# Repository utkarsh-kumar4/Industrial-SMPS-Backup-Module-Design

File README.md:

<h1>⚡ Industrial SMPS Backup Module Design ⚡</h1>

<h2>Project Premise</h2>
<p>
This project implements a reliable SMPS-based backup system designed to provide clean and stable DC power to industrial electronics such as PLCs, HMIs, sensors, and low-voltage control circuits. In industrial environments, especially in oil & gas, power generation, and transmission systems, voltage stability and low ripple are critical for the safe and accurate operation of automation and control devices. 
The system combines a <strong>TLV61048 boost converter</strong> with a <strong>TLV767-1A LDO regulator</strong> to deliver both voltage elevation and high-quality regulation, ensuring operational reliability even under fluctuating input conditions.
</p>

<h2>Technical Rationale for Module Selection</h2>
<p>
The <strong>TLV61048</strong> was selected for its ability to efficiently boost a low-voltage battery input (e.g., 3.7–12V Li-ion) to the required system bus voltage, maintaining continuous operation even during battery discharge. Its high efficiency (up to 95%) minimizes energy loss and heat generation, which is critical in compact backup systems.  
The <strong>TLV767-1A LDO regulator</strong> is used to post-regulate the boosted voltage, providing low-noise, stable DC output. This stage is essential because boost converters inherently produce high-frequency ripple, which can disrupt sensitive electronics. By combining these stages, the design achieves both efficient energy conversion and superior voltage quality.
</p>

<h2>System Architecture and Operation</h2>
<p>
The architecture consists of two primary stages:
<ul>
  <li><strong>Boost Stage:</strong> Elevates battery voltage to a constant bus voltage suitable for downstream devices, compensating for battery voltage drops.</li>
  <li><strong>LDO Stage:</strong> Smooths out high-frequency ripple and maintains precise voltage regulation for sensitive electronics, preventing errors or failures in industrial control systems.</li>
</ul>
</p>
<p>
The configuration is practical and feasible for real-world deployment. It is compatible with typical industrial load currents (~400 mA) and can be scaled or paralleled for higher current requirements. The modular design allows easy integration into existing control panels or standalone backup units.
</p>

<h2>Feasibility and Industrial Relevance</h2>
<p>
This architecture mirrors industrial backup and power conditioning solutions used in PSUs and process industries:
<ul>
  <li><strong>Process Automation:</strong> PLCs and HMIs in oil refineries, chemical plants, and power stations rely on clean DC supply for accurate sensing, control loops, and HMI interfaces.</li>
  <li><strong>Critical Control Systems:</strong> In power generation or transmission, transient voltage fluctuations can cause trips, errors, or equipment damage. Boost + LDO solutions provide resilience against such disturbances.</li>
  <li><strong>Modular and Scalable:</strong> Multiple units can be deployed for redundant backup, a standard practice in NTPC, PGCIL, and industrial control systems to maintain uptime and operational reliability.</li>
  <li><strong>Energy Efficiency:</strong> High-efficiency boost conversion reduces battery draw and heat, making it viable for continuous industrial operation without excessive thermal management.</li>
</ul>
</p>
<p>
In essence, the project demonstrates the feasibility of combining power electronics for **both voltage reliability and quality**, which is a direct requirement in current industrial environments. It also provides a foundation for extending the system with features like digital monitoring, SCADA integration, or automated load switching.
</p>

<h2>Advantages ✅</h2>
<ul>
  <li>Stable voltage output under varying battery conditions.</li>
  <li>High-quality ripple suppression for sensitive electronics.</li>
  <li>Compact, modular, and scalable design suitable for industrial panels.</li>
  <li>Energy-efficient solution aligned with industrial best practices.</li>
</ul>

<h2>Limitations ⚠️</h2>
<ul>
  <li>Maximum current output is limited by LDO ratings (~400 mA); higher loads require multiple units or alternative LDOs.</li>
  <li>Minor efficiency loss in the LDO stage, especially at higher currents.</li>
  <li>Thermal management is necessary for continuous operation at full load.</li>
</ul>

<h2>Future Extensions 🔧</h2>
<p>
This design can be extended to include:
<ul>
  <li>Digital voltage/current monitoring using microcontrollers.</li>
  <li>Automated battery load management for longer backup durations.</li>
  <li>Integration with plant SCADA or IoT systems for real-time monitoring and diagnostics.</li>
  <li>Redundant parallel operation for critical industrial applications.</li>
</ul>
</p>

<h2>References 📚</h2>
<ul>
  <li><a href="https://www.ti.com/lit/ds/symlink/tlv61048.pdf">TLV61048 Datasheet</a></li>
  <li><a href="https://www.ti.com/lit/ds/symlink/tlv767.pdf">TLV767-1A Datasheet</a></li>
  <li>Texas Instruments Application Notes for SMPS + LDO integration</li>
</ul>

<h2>📷 Project Images</h2>
<h2>TLV61048: Boost Converter</h2>
<h3>🔹 Schematic Design</h3>

<h3>🔹 PCB Layout</h3>

<h3>🔹 3D Board View</h3>

<h2>TLV7607DRVx: LDO Regulator</h2>
<h3>🔹 Linear Regulator</h3>

<h3>🔹 Schematic Design</h3>

<h3>🔹 PCB Layout</h3>

<h3>🔹 3D Board View</h3>

<h2>Author 👤</h2>
<p><a href="https://github.com/utkarsh-kumar4">Utkarsh Kumar</a> 👨🏻‍💻🎓</p>

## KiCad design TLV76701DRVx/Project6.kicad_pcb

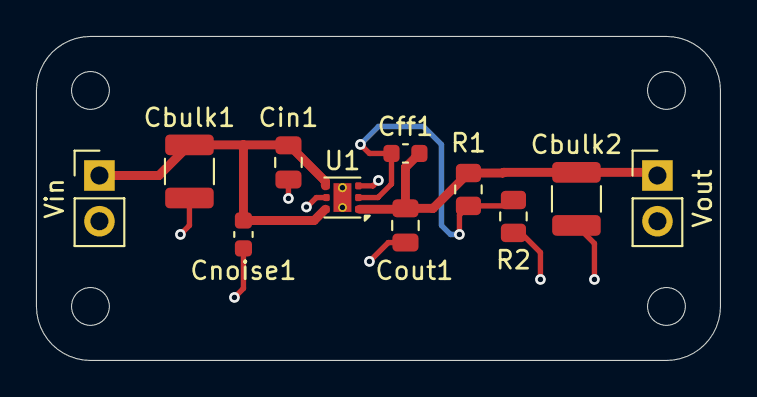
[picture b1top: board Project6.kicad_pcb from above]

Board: 2 copper layers, 38.0 x 18.0 mm, 15 parts (0 on the bottom side), 4 nets.

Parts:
Cbulk1, Cbulk2: 10uF; C_1210_3225Metric
Cff1: 10pF; C_0603_1608Metric
Cin1: 1uF; C_0805_2012Metric
Cnoise1: 100nF; C_0603_1608Metric
Cout1: 2.2uF; C_0805_2012Metric
H1, H2, H3, H4: MountingHole; MountingHole_2.1mm
R1: 226k; R_0805_2012Metric
R2: 16.2k; R_0805_2012Metric
U1: TLV76701DRVx; WSON-6-1EP_2x2mm_P0.65mm_EP1x1.6mm_ThermalVias
Vin: Conn_01x02_Pin; PinHeader_1x02_P2.54mm_Vertical
Vout: Conn_01x02_Pin; PinHeader_1x02_P2.54mm_Vertical

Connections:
/FB: Cff1.2, R1.2, R2.1, U1.2 (FB)
/GND: Cbulk1.2, Cbulk2.2, Cin1.2, Cnoise1.2, Cout1.2, R2.2, U1.3 (GND), U1.5 (GND), U1.7 (PAD), Vin.2, Vout.2
/Vin: Cbulk1.1, Cin1.1, Cnoise1.1, U1.4 (EN), U1.6 (IN), Vin.1
/Vout: Cbulk2.1, Cff1.1, Cout1.1, R1.1, U1.1 (OUT), Vout.1

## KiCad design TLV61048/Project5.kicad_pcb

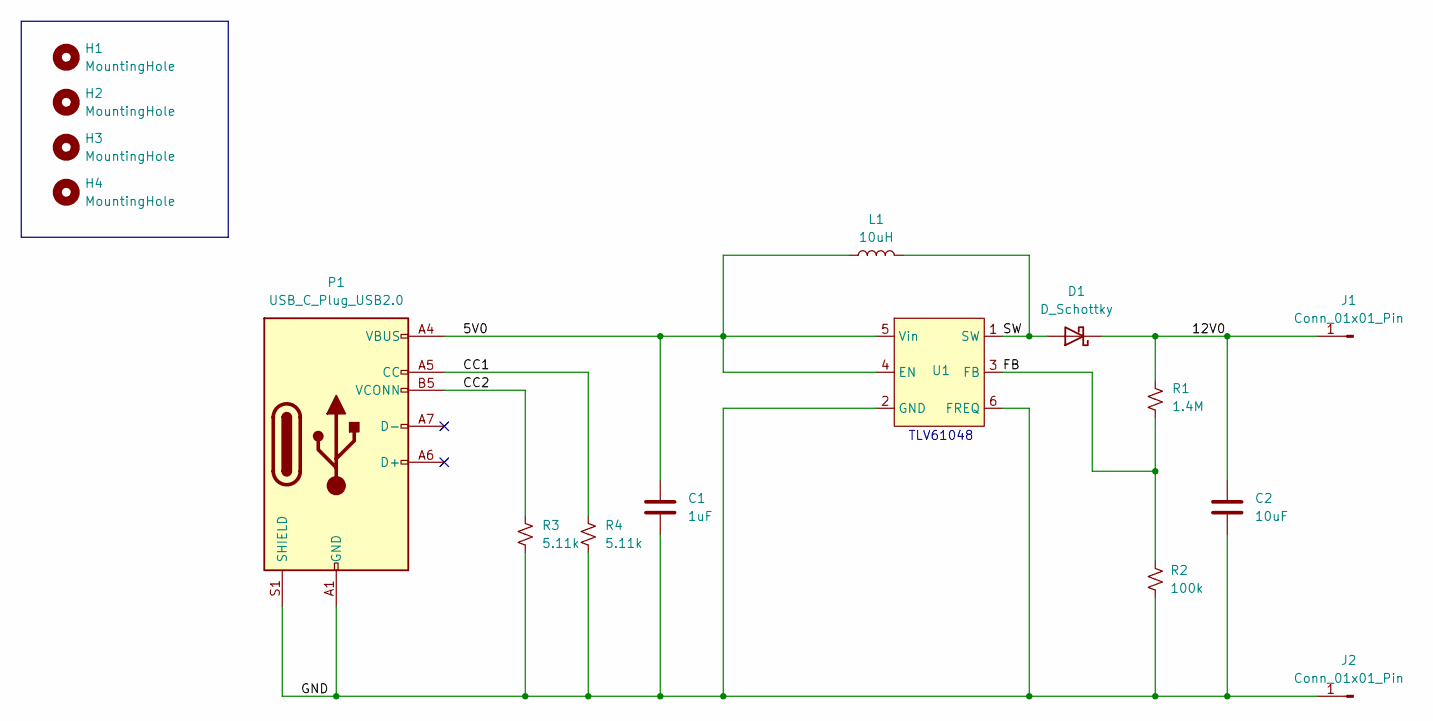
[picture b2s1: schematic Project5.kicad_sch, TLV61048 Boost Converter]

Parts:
C1: 1uF; C_1206_3216Metric
C2: 10uF; C_1206_3216Metric
D1: D_Schottky; D_SOD-123
H1, H2, H3, H4: MountingHole; MountingHole_2.1mm
J1, J2: Conn_01x01_Pin; PinHeader_1x01_P2.54mm_Vertical
L1: 10uH; L_Bourns-SRN8040_8x8.15mm
P1: USB_C_Plug_USB2.0; USB_C_Receptacle_GCT_USB4105-xx-A_16P_TopMnt_Horizontal
R1: 1.4M; R_0402_1005Metric_Pad0.72x0.64mm_HandSolder
R2: 100k; R_0402_1005Metric_Pad0.72x0.64mm_HandSolder
R3, R4: 5.11k; R_0603_1608Metric
U1: SOT-23-6

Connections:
/5V0: C1.1, L1.1, P1.A4 (VBUS), P1.A9 (VBUS), P1.B4 (VBUS), P1.B9 (VBUS), U1.4 (EN), U1.5 (Vin)
/12V0: C2.1, D1.1 (K), J1.1, R1.2
/CC1: P1.A5 (CC), R4.1
/CC2: P1.B5 (VCONN), R3.1
/FB: R1.1, R2.2, U1.3 (FB)
/GND: C1.2, C2.2, J2.1, P1.A1 (GND), P1.A12 (GND), P1.B1 (GND), P1.B12 (GND), P1.S1 (SHIELD), R2.1, R3.2, R4.2, U1.2 (GND), U1.6 (FREQ)
/SW: D1.2 (A), L1.2, U1.1 (SW)

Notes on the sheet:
TLV61048

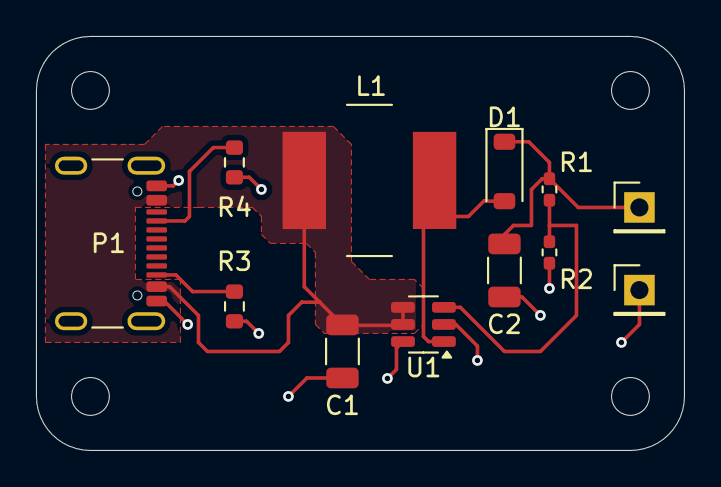
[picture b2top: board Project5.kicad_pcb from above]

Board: 2 copper layers, 36.0 x 23.0 mm, 16 parts (0 on the bottom side), 7 nets.
